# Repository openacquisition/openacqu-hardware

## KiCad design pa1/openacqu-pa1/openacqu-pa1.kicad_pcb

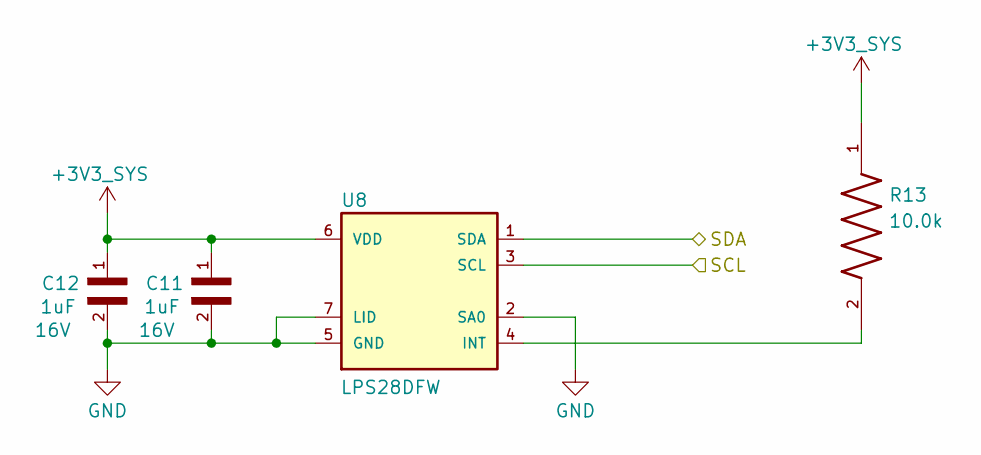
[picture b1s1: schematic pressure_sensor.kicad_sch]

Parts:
C11, C12: 1uF; CAPC1005X55N; Voltage 16V
R13: 10.0k; RESC1005X40N; PARTREV V.12
U8: LPS28DFW; CCLGA-7L; MPN LPS28DFW

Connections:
+3V3_SYS: C11.1, C12.1, R13.1, U8.6 (VDD); also elsewhere on the board
/Core/SCL: U8.3 (SCL); also elsewhere on the board
/Core/SDA: U8.1 (SDA); also elsewhere on the board
GND: C11.2, C12.2, U8.2 (SA0), U8.5 (GND), U8.7 (LID); also elsewhere on the board
unnamed: R13.2, U8.4 (INT)

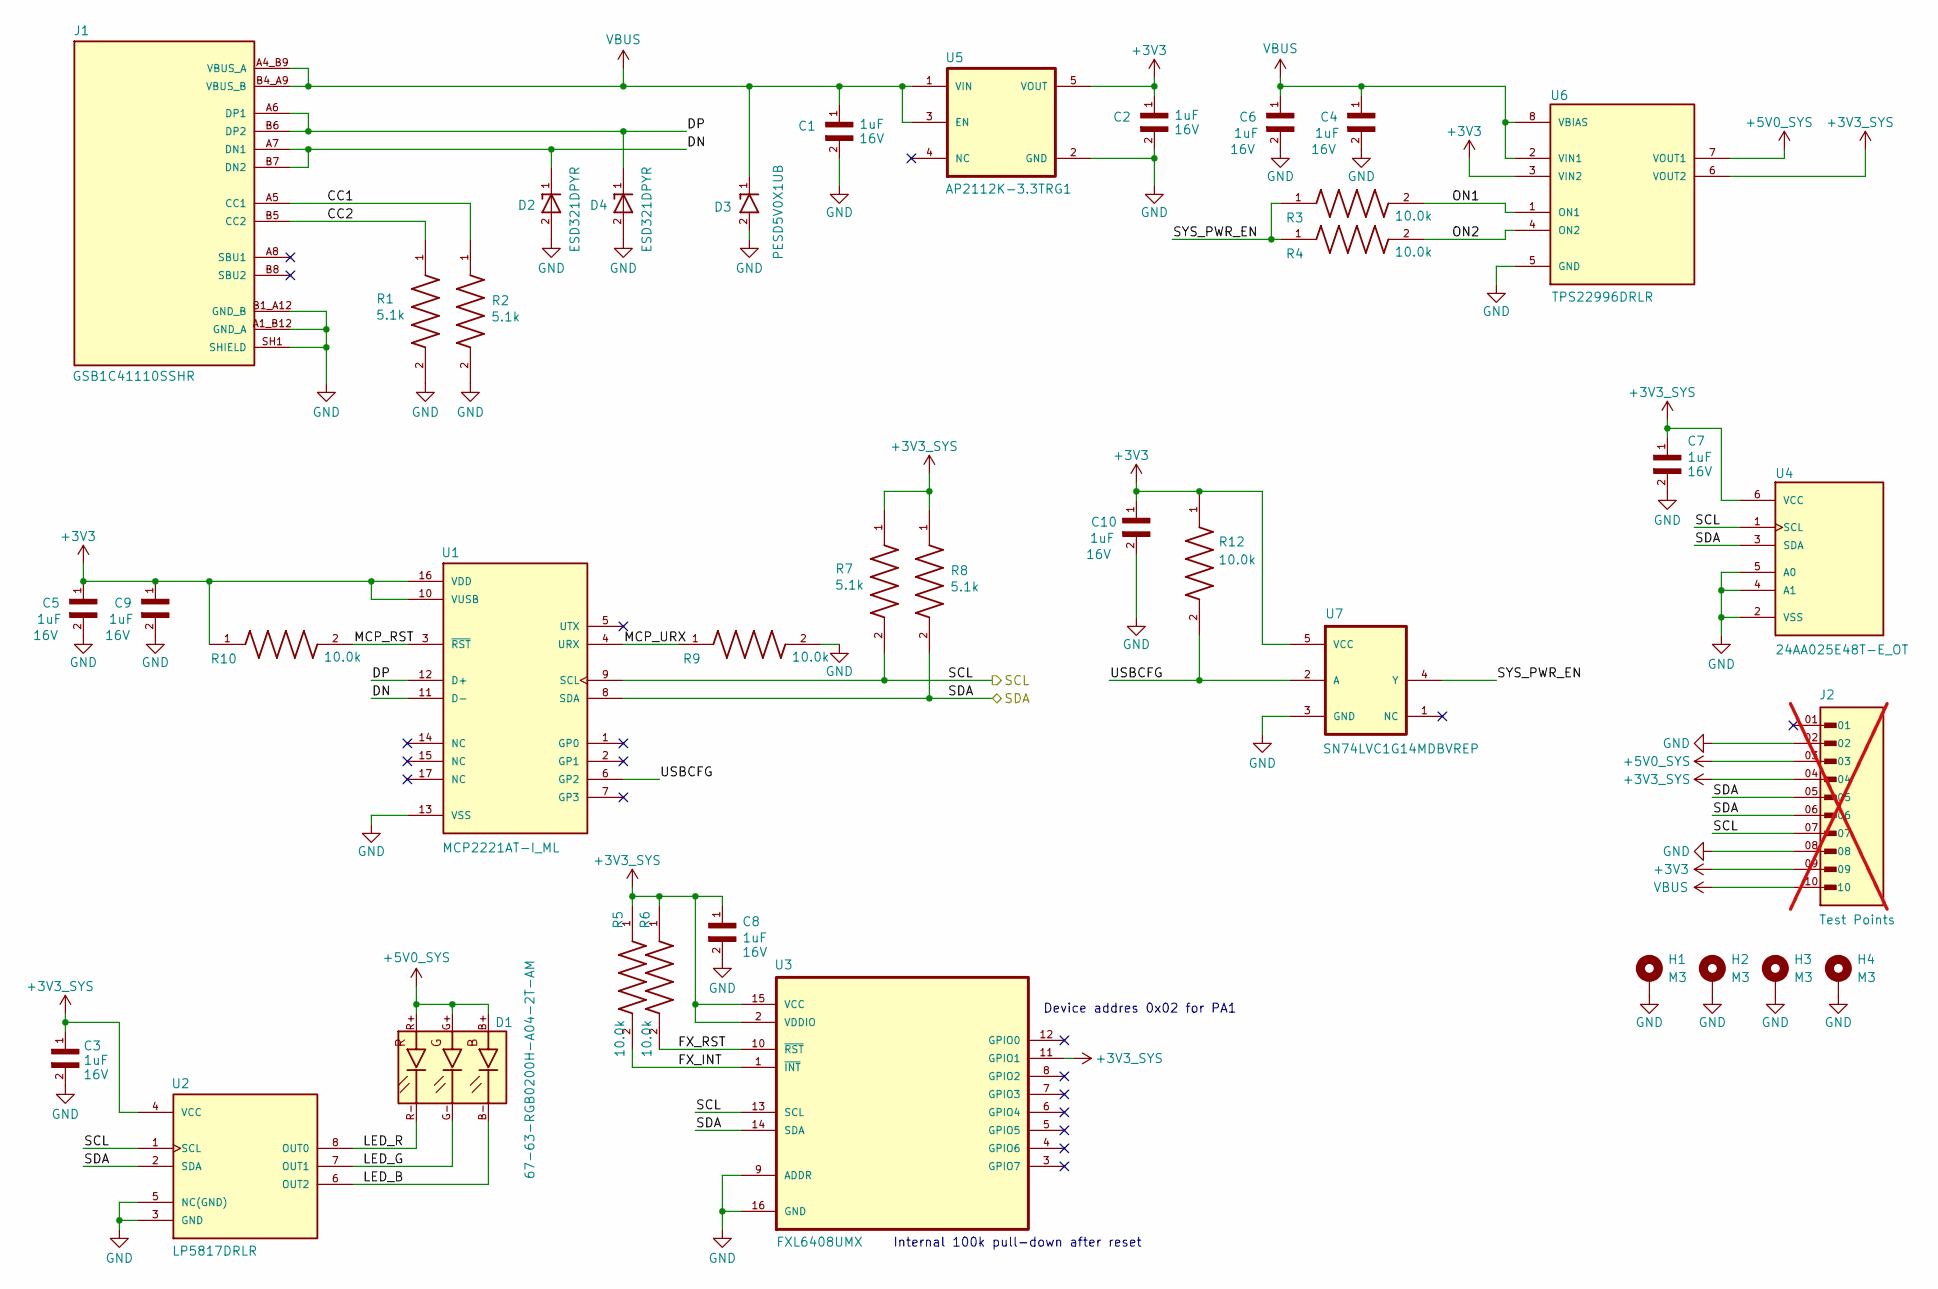
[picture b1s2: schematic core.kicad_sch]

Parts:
C1, C2, C3, C4, C5, C6, C7, C8, C9, C10: 1uF; CAPC1005X55N; Voltage 16V
D1: 67-63-RGB0200H-A04-2T-AM; EVERLIGHT_67-63_PLCC6; JLCPN C7433198
D2, D4: ESD321DPYR; TVS_ESD321DPYR; PARTREV B
D3: PESD5V0X1UB; SOD523
H1, H2, H3, H4: M3; MountingHole_3.5mm_Pad
J1: GSB1C41110SSHR; AMPHENOL_GSB1C41110SSHR; PARTREV AX1
J2: Test Points; MLE_TSHC-110-S-14-295-G-LF; not fitted
R1, R2, R7, R8: 5.1k; RESC1005X40N
R3, R4, R5, R6, R9, R10, R12: 10.0k; RESC1005X40N; PARTREV V.12
U1: MCP2221AT-I_ML; PARTREV Rev D
U2: LP5817DRLR; IC_LP5817DRLR; PARTREV MARCH 2025
U3: FXL6408UMX; QFN40P260X180X55-16N; PART_REV 1.0.0
U4: 24AA025E48T-E_OT; SOT95P270X145-6N; PARTREV G
U5: AP2112K-3.3TRG1; SOT95P285X140-5N; PARTREV 2-2
U6: TPS22996DRLR; IC_TPS22996DRLR; PARTREV Rev. A; JLCPN C34640248
U7: SN74LVC1G14MDBVREP; SOT95P280X145-5N; MPN SN74LVC1G14MDBVREP

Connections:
+3V3: C2.1, C5.1, C9.1, C10.1, J2.09, R10.1, R12.1, U1.10 (VUSB), U1.16 (VDD), U5.5 (VOUT), U6.3 (VIN2), U7.5 (VCC)
+3V3_SYS: C3.1, C7.1, C8.1, J2.04, R5.1, R6.1, R7.1, R8.1, U2.4 (VCC), U3.2 (VDDIO), U3.11 (GPIO1), U3.15 (VCC), U4.6 (VCC), U6.6 (VOUT2); also elsewhere on the board
+5V0_SYS: D1.B+, D1.G+, D1.R+, J2.03, U6.7 (VOUT1)
/Core/CC1: J1.A5 (CC1), R2.1
/Core/CC2: J1.B5 (CC2), R1.1
/Core/DN: D2.1, J1.A7 (DN1), J1.B7 (DN2), U1.11 (D-)
/Core/DP: D4.1, J1.A6 (DP1), J1.B6 (DP2), U1.12 (D+)
/Core/FX_INT: R5.2, U3.1 (~INT)
/Core/FX_RST: R6.2, U3.10 (~RST)
/Core/LED_B: D1.B-, U2.6 (OUT2)
/Core/LED_G: D1.G-, U2.7 (OUT1)
/Core/LED_R: D1.R-, U2.8 (OUT0)
/Core/MCP_RST: R10.2, U1.3 (~RST)
/Core/MCP_URX: R9.1, U1.4 (URX)
/Core/ON1: R3.2, U6.1 (ON1)
/Core/ON2: R4.2, U6.4 (ON2)
/Core/SCL: J2.07, R7.2, U1.9 (SCL), U2.1 (SCL), U3.13 (SCL), U4.1 (SCL); also elsewhere on the board
/Core/SDA: J2.05, J2.06, R8.2, U1.8 (SDA), U2.2 (SDA), U3.14 (SDA), U4.3 (SDA); also elsewhere on the board
/Core/SYS_PWR_EN: R3.1, R4.1, U7.4 (Y)
/Core/USBCFG: R12.2, U1.6 (GP2), U7.2 (A)
GND: C1.2, C2.2, C3.2, C4.2, C5.2, C6.2, C7.2, C8.2, C9.2, C10.2, D2.2, D3.2, D4.2, H1.1 (1_1), H2.1 (1_1), H3.1 (1_1), H4.1 (1_1), J1.A1_B12 (GND_A), J1.B1_A12 (GND_B), J1.SH1 (SHIELD), J1.SH2 (SHIELD), J1.SH3 (SHIELD), J1.SH4 (SHIELD), J2.02, J2.08, R1.2, R2.2, R9.2, U1.13 (VSS), U2.3 (GND), U2.5 (NC(GND)), U3.9 (ADDR), U3.16 (GND), U4.2 (VSS), U4.4 (A1), U4.5 (A0), U5.2 (GND), U6.5 (GND), U7.3 (GND); also elsewhere on the board
VBUS: C1.1, C4.1, C6.1, D3.1, J1.A4_B9 (VBUS_A), J1.B4_A9 (VBUS_B), J2.10, U5.1 (VIN), U5.3 (EN), U6.2 (VIN1), U6.8 (VBIAS)

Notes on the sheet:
Internal 100k pull-down after reset
Device addres 0x02 for PA1

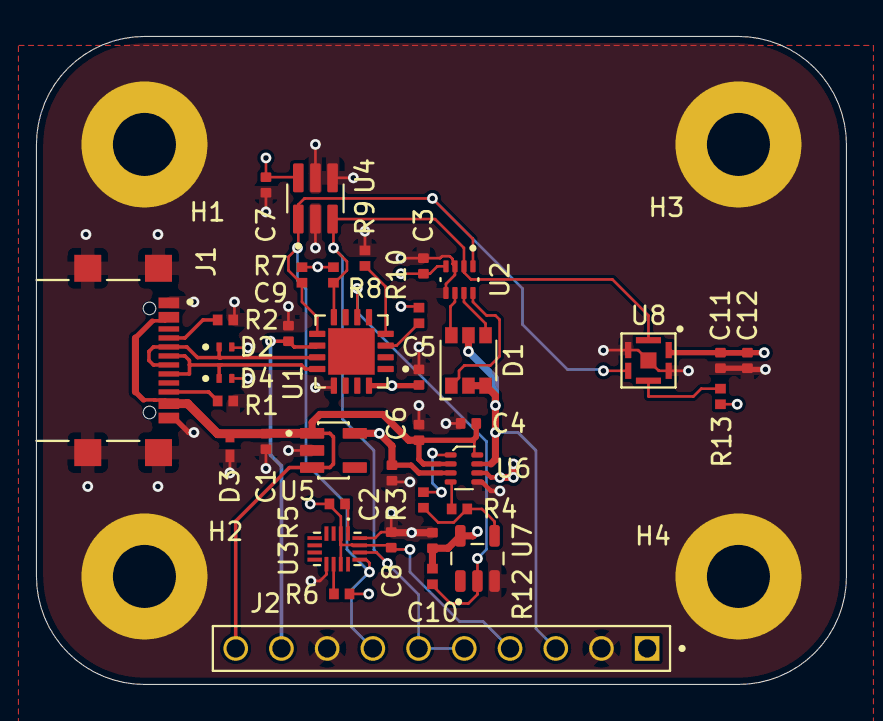
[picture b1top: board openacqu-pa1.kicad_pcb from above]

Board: 4 copper layers, 45.0 x 36.0 mm, 42 parts (0 on the bottom side), 23 nets.

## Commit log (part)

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2026-02-03 Added gitignore for KiCAD projects
2026-04-24 Initial commit of the core schematic and library parts
2026-04-24 Core placement and 3D models
2026-04-24 Added .gitignore to allow step files in libraries
2026-04-24 Adding library parts for temp probe
2026-04-26 Routed core design
2026-04-26 Moved core to separate sheet
2026-04-26 Inherited core to tmp1
2026-04-26 Added sensor to tmp1
2026-05-28 Completed layout for the TMP1
2026-05-28 Added stitcing vias
2026-05-29 Updated symbols with JLCPCB part numbers
2026-05-29 Updated 0402 footprint for 100 ohm resistor
2026-05-30 Initial commit of dev board design forked from core
2026-05-30 Placement and routing complete for DEV1
2026-06-17 Updated to KiCAD v10
2026-06-17 Added outputs/ to .gitignore
